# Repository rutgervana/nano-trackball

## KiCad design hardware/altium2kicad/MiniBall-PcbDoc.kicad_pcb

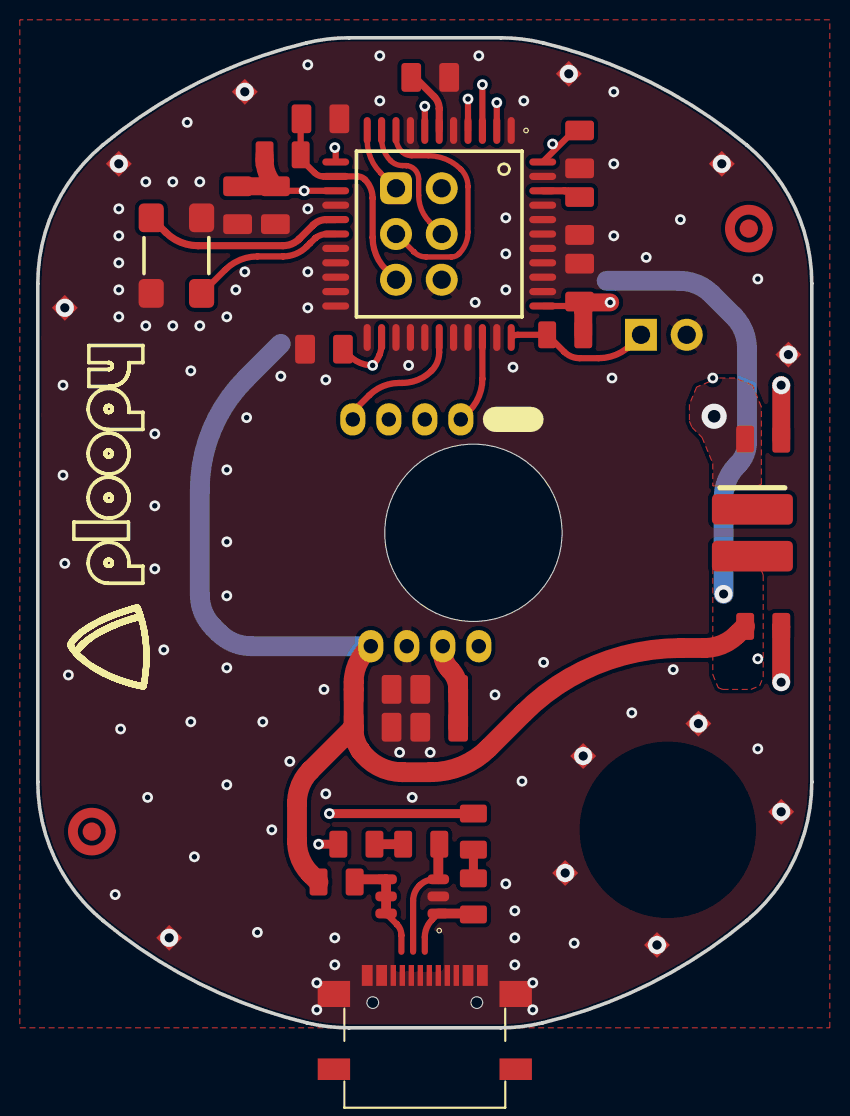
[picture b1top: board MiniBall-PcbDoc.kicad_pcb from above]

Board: 4 copper layers, 43.0 x 55.0 mm, 44 parts (0 on the bottom side), 24 nets.

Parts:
C1, C2, C3, C4, C5, C6, C7, C8, C9, C10, C11, C22: 0805, X5R or better; 0805 - TALL
D1: Red/Orange/Yellow Side-facing SMT LEDs, high brig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; SIDELED-A67F
FB1, FB2, FB3: FERRITE BEAD 600 OHM 0805 1LN; 0805
FID1, FID2: IPC-7351 Fiducial 1mm; FIDUCIAL_1.5
J1: 6-pin 0.100" ICSP header; 6x2
J2: CONN RCPT USB2.0 MICRO B SMD R/A; USB_C_Receptacle_China_SMT
J3: 2-pin 0.100" header; 2x1
LOGO1: PloopyLogo
R1, R3, R4, R5, R6, R7: Chip resistor; 0805
SP1, SP2, SP3, SP4, SP5, SP6, SP7, SP8, SP9, SP10, SP11, SP12: Open square pad for spark gapping; SparkGap
U1: IC MCU 8BIT 32KB FLASH 44TQFP; ATmega32U4 - TQFP80P1200X1200X120-44N
U2: Optical Mouse Navigation Sensor; ADNS-5050
Y1: 16MHz Crystal 12pF 100 Ohms 4-SMD, No Lead; LFXTAL055663BULK
Z1: TVS DIODE 5.5V 6TSOP (Low capacitance, USB); PESD3V3S4UD - SOT95P275X110-6N

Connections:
GND: C1.1, C2.1, C3.1, C4.1, C5.1, C6.1, C7.1, C8.1, C9.1, C10.1, C11.1, C22.1, J1.6, J3.2, SP1.1, SP2.1, SP3.1, SP4.1, SP5.1, SP6.1, SP7.1, SP8.1, SP9.1, SP10.1, SP11.1, SP12.1, U1.1, U1.5, U1.8, U1.15, U1.18, U1.19, U1.20, U1.21, U1.22, U1.23, U1.25, U1.26, U1.27, U1.29, U1.30, U1.32, U1.35, U1.36, U1.37, U1.38, U1.39, U1.40, U1.41, U1.43, U2.6, Y1.2, Y1.4, Z1.2
MISO: J1.1, U1.11
MOSI: J1.4, U1.10
NetMCU.C.1_2: C1.2, U1.6
NetMCU.C.4_2: C4.2, U1.42
NetMCU.J.3_1: J3.1, R5.1, U1.33
NetMCU.U.1_3: R6.2, U1.3
NetMCU.U.1_4: R7.2, U1.4
NetMCU.U.1_12: U1.12, U2.8
NetMCU.U.1_16: U1.16, Y1.1
NetMCU.U.1_17: U1.17, Y1.3
NetMCU.U.1_28: U1.28, U2.4
NetMCU.U.1_31: U1.31, U2.1
NetMOS.C.2_2: C2.2, C3.2, U2.7
NetMOS.D.1_C: D1.C, R4.1, U2.2
NetMOS.R.3_1: R3.1, R4.2
NetUSB.FB.1_1: FB1.1, Z1.4, Z1.5, Z1.6
NetUSB.FB.2_1: FB2.1, Z1.3
NetUSB.FB.2_2: FB2.2, R6.1
NetUSB.FB.3_1: FB3.1, Z1.1
NetUSB.FB.3_2: FB3.2, R7.1
RESET: C22.2, J1.5, R1.1, U1.13, U2.3
SCLK: J1.3, U1.9
V_USB: C5.2, C6.2, C7.2, C8.2, C9.2, C10.2, C11.2, D1.A, FB1.2, J1.2, R1.2, R3.2, R5.2, U1.2, U1.7, U1.14, U1.24, U1.34, U1.44, U2.5

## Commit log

2021-09-12 Converted to Kicad
